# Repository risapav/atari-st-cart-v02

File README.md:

# Atari ST ROM Cartridge v2 — 2× W29C040-90B (16-bit)

**KiCad 10 project · Rev 1.2 · 2026-11-26 · risapav**  
https://github.com/risapav/atari-st-cart-v02

A read-only ROM cartridge PCB for the Atari ST/STE/Mega family.  
Two Winbond W29C040-90B Flash EEPROMs work in parallel to provide a full 16-bit data bus.  
A 4-position DIP switch (positions 1–3 active, position 4 unconnected) selects one of 8 banks of 128 KB, giving up to **1 MB** of banked ROM storage.

---

## Features

| Feature | Detail |
|---|---|
| Data bus | 16-bit (U1 → D0–D7 low byte, U2 → D8–D15 high byte) |
| ROM chips | 2× Winbond W29C040-90B (512 K × 8, DIP-32, 90 ns) |
| Total capacity | 1 MB (8 banks × 128 KB) |
| Address window | `$FA0000`–`$FBFFFF` (256 KB visible at once) |
| Bank switching | 4-bit DIP switch (SW1), positions 1–3 on chip A16–A18 (position 4 NC) |
| Chip select | Wired-AND of /ROM3 + /ROM4 via BAT42 diodes + 4.7 kΩ pull-up |
| Write-protect | /WE pulled to +5 V via R5 (10 kΩ) — the ST cannot write to the chip |
| Board size | 47.5 × 90.2 mm overall (42 mm-wide edge connector tongue) |
| Connector | 40-pin dual-row edge connector, 2 mm pitch (Atari CB101494) |

---

## Address Mapping

The Atari ST 68000 CPU does not expose A0 — byte selection is done through /UDS and /LDS.  
The cartridge port provides A1–A15, /ROM3, /ROM4, /UDS, /LDS, D0–D15.

```
ST bus signal   →   W29C040 pin
─────────────────────────────────
A1  – A15       →   A0  – A14   (15 bits)
/ROM4           →   A15         (0 = $FA bank, 1 = $FB bank)
SW1-1 (A16)     →   A16         ┐
SW1-2 (A17)     →   A17         ├ bank select (8 banks)
SW1-3 (A18)     →   A18         ┘
/ROM3 AND /ROM4 →   /CE (both chips, wired-AND)
/UDS            →   /OE on U2 (D8–D15, high byte chip)
/LDS            →   /OE on U1 (D0–D7, low byte chip)
/WE             →   ROM_~{WE} → R5 (10 kΩ) → +5V    write-protect
```

The full 256 KB window (`$FA0000`–`$FBFFFF`) is split by the /ROM4 signal:

| /ROM4 | /ROM3 | Region | Chip A15 |
|---|---|---|---|
| LOW  | HIGH | `$FA0000`–`$FAFFFF` | 0 |
| HIGH | LOW  | `$FB0000`–`$FBFFFF` | 1 |

Both chips are enabled only when **both** /ROM3 and /ROM4 are asserted (wired-AND through D1, D2).

---

## Bank Selection (DIP Switch SW1)

Switch closed = 0 (GND via switch) · Switch open = 1 (pulled to +5 V via 10 kΩ)

| SW1-3 | SW1-2 | SW1-1 | Bank | Offset in chip |
|---|---|---|---|---|
| 0 | 0 | 0 | 0 | 0x000000 |
| 0 | 0 | 1 | 1 | 0x010000 |
| 0 | 1 | 0 | 2 | 0x020000 |
| 0 | 1 | 1 | 3 | 0x030000 |
| 1 | 0 | 0 | 4 | 0x040000 |
| 1 | 0 | 1 | 5 | 0x050000 |
| 1 | 1 | 0 | 6 | 0x060000 |
| 1 | 1 | 1 | 7 | 0x070000 |

Each bank holds 128 KB visible through the ST cartridge window.  
U1 and U2 must be programmed independently (each chip carries one byte of every 16-bit word).  
Each chip holds 64 KB per bank (0x10000 bytes); the combined 16-bit content per bank is 128 KB.

---

## Bill of Materials

| Ref | Value / Part | Package | LCSC | Note |
|---|---|---|---|---|
| U1, U2 | Winbond W29C040-90B | DIP-32 W15.24 mm | C2331 | 512 K × 8 Flash EEPROM; U1 = low byte (D0–D7, /LDS), U2 = high byte (D8–D15, /UDS) |
| J1 | Atari ST cartridge port | 2×20 edge, 2 mm pitch | — | CB101494 compatible |
| SW1 | 4-pos slide DIP switch (pin 4 NC) | THT W7.62 mm P2.54 mm | — | bank select A16–A18 on positions 1–3 |
| D1, D2 | BAT42 | SOD-123 SMD | C134396 | wired-AND for /CE |
| R1 | 10 kΩ | 0805 SMD | C100047 | pull-up for chip A16 |
| R2 | 10 kΩ | 0805 SMD | C100047 | pull-up for chip A17 |
| R3 | 10 kΩ | 0805 SMD | C100047 | pull-up for chip A18 (also VPP for TC57H1000) |
| R4 | 4.7 kΩ | 0805 SMD | C60816 | pull-up on /CE wired-AND node |
| R5 | 10 kΩ | 0805 SMD | C100047 | pull-up for /WE (ROM_~{WE}) |
| C1, C2 | 100 nF | 0805 SMD | C83055 | decoupling, one per chip |
| C3 | 22 µF | THT radial D5 mm P2 mm | C43845 | bulk decoupling |
| JP1 | SolderJumper_2_Open | SMD 2-pad | — | bank-select tie-off; keep OPEN when using TC57H1000AD |

### Alternative chip: TC57H1000AD-85

The TC57H1000AD-85 (Toshiba 1 M × 8 SRAM) can be substituted with these adjustments:

| SW1 position | Setting | Reason |
|---|---|---|
| SW1-3 (A18 / VPP) | **open** | VPP must be +5 V; R3 pull-up provides this |
| SW1-2 (A17 / pin 30) | ignore | pin 30 is NC on TC57H1000 |
| SW1-1 (A16) | as desired | active bank select |

---

## Chip Enable Logic

```
/ROM3 ──|<|── D2 ──┬── R4 ── +5V
                   │
/ROM4 ──|<|── D1 ──┴── /CE (U1 pin 22, U2 pin 22)
```

`|<|` = Cathode (K) on the signal side, Anode (A) on the /CE node side.

Diodes D1 and D2 perform a passive wired-OR on active-low signals: /CE goes LOW whenever **either** /ROM3 or /ROM4 is LOW.  
When both signals are HIGH (no access), R4 (4.7 kΩ) holds /CE HIGH (chips deselected).  
In practice /ROM3 and /ROM4 are never both LOW simultaneously on the ST bus, so this effectively enables the chips when EITHER region is accessed.

---

## Repository Contents

```
cart_v02/
├── cart_v02.kicad_pro      — KiCad 10 project file
├── cart_v02.kicad_sch      — schematic
├── cart_v02.kicad_pcb      — PCB layout
├── my-libs/                — project-local symbol and footprint libraries
├── production/             — fabrication output (rev 1.1)
│   ├── Atari_ST_ROM_Cartridge_v2__2_W29C040-90B_16-bit_1.2.zip
│   ├── bom.csv
│   ├── designators.csv
│   ├── netlist.ipc
│   ├── positions.csv
│   └── JLCPCB_ORDER.md     — JLCPCB order parameters and procedure
├── tools/                  — Python scripts for ROM image preparation
│   ├── chips.py            — chip definitions (W29C040, TC57H1000)
│   ├── rom_pack.py         — pack directory or file list → chip files (STC auto-strip)
│   ├── rom_split.py        — split combined 16-bit image → LO + HI
│   ├── rom_info.py         — display bank map and chip statistics
│   ├── rom_validate.py     — validate ROM files (.bin/.stc/.rom/.img): size, magic, STC strip
│   ├── Makefile            — shortcuts: pack / split / info / validate (PRGDIR=prg/)
│   ├── README.md           — full tool documentation (SK)
│   ├── README_en.md        — full tool documentation (EN)
│   └── prg/                — source ROM images (default input for make pack)
├── doc/
│   ├── functional_analysis.md    — address decoding, CE logic, ROM formats (EN)
│   └── functional_analysis_sk.md — address decoding, CE logic, ROM formats (SK)
└── test/                   — virtual cartridge simulation (Python)
    ├── cartridge_model.py  — hardware model of the cartridge bus
    ├── generate_test_roms.py
    ├── run_tests.py        — 73 tests: address decode, bank switch, CE logic
    └── TESTING.md          — test methodology and results
```

### KiCad library dependency

Custom symbols and footprints are bundled inside `my-libs/` and referenced with `${KIPRJMOD}` paths in `fp-lib-table` and `sym-lib-table`.  
No global library installation is needed — just open `cart_v02.kicad_pro` directly.

---

## Programming the Chips

Each chip is 512 K × 8 and must be programmed **out of circuit** (remove from DIP socket).

The `tools/` directory contains Python scripts that automate all preparation steps:

Place all source ROM images (`.bin`, `.rom`, `.img`, `.stc`) into `tools/prg/`.
The tools use this directory as the default source location.

```bash
cd tools/

# Validate source images
python3 rom_validate.py prg/

# Pack all images from prg/ → chip files  (directory scanned automatically,
# filenames with spaces handled correctly, Steem .STC headers stripped)
make pack
# — or equivalently: python3 rom_pack.py prg/
# → writes prg/pack_order.txt and out/bank{N}_{original_name} copies

# Display bank map and chip signatures
python3 rom_info.py out/chip_u1_lo.bin out/chip_u2_hi.bin
```

**To reorder banks:** edit `prg/pack_order.txt` (one filename per line) and run `make pack` again.  
The numbered copies in `out/bank{N}_*` always reflect the current bank assignment.

Or with an explicit file list / different directory:

```bash
make pack PRGDIR=myroms/
make pack SRCS="game.bin other.rom"   # no spaces in filenames
```

Manual procedure (without scripts):

1. Prepare two binary files by de-interleaving the combined ROM image:
   - `chip_u1_lo.bin` — odd bytes (D0–D7, lower byte) → **U1**
   - `chip_u2_hi.bin` — even bytes (D8–D15, upper byte) → **U2**
2. For a banked image, place each bank at offset `bank × 0x10000` in each chip file.
3. Program each chip file into the respective chip using any W29C040-compatible EEPROM programmer.
4. Insert chips with correct orientation (pin 1 at the notch end).
5. Set SW1 to the desired bank.

> The W29C040-90B supports in-system Software Data Protection (SDP).  
> Disable SDP before programming if your programmer requires it.

See `tools/README_en.md` (EN) or `tools/README.md` (SK) for full documentation including TC57H1000AD-85 support.

---

## License

Hardware design released under [CERN-OHL-P v2](https://ohwr.org/cern_ohl_p_v2.txt) (permissive).

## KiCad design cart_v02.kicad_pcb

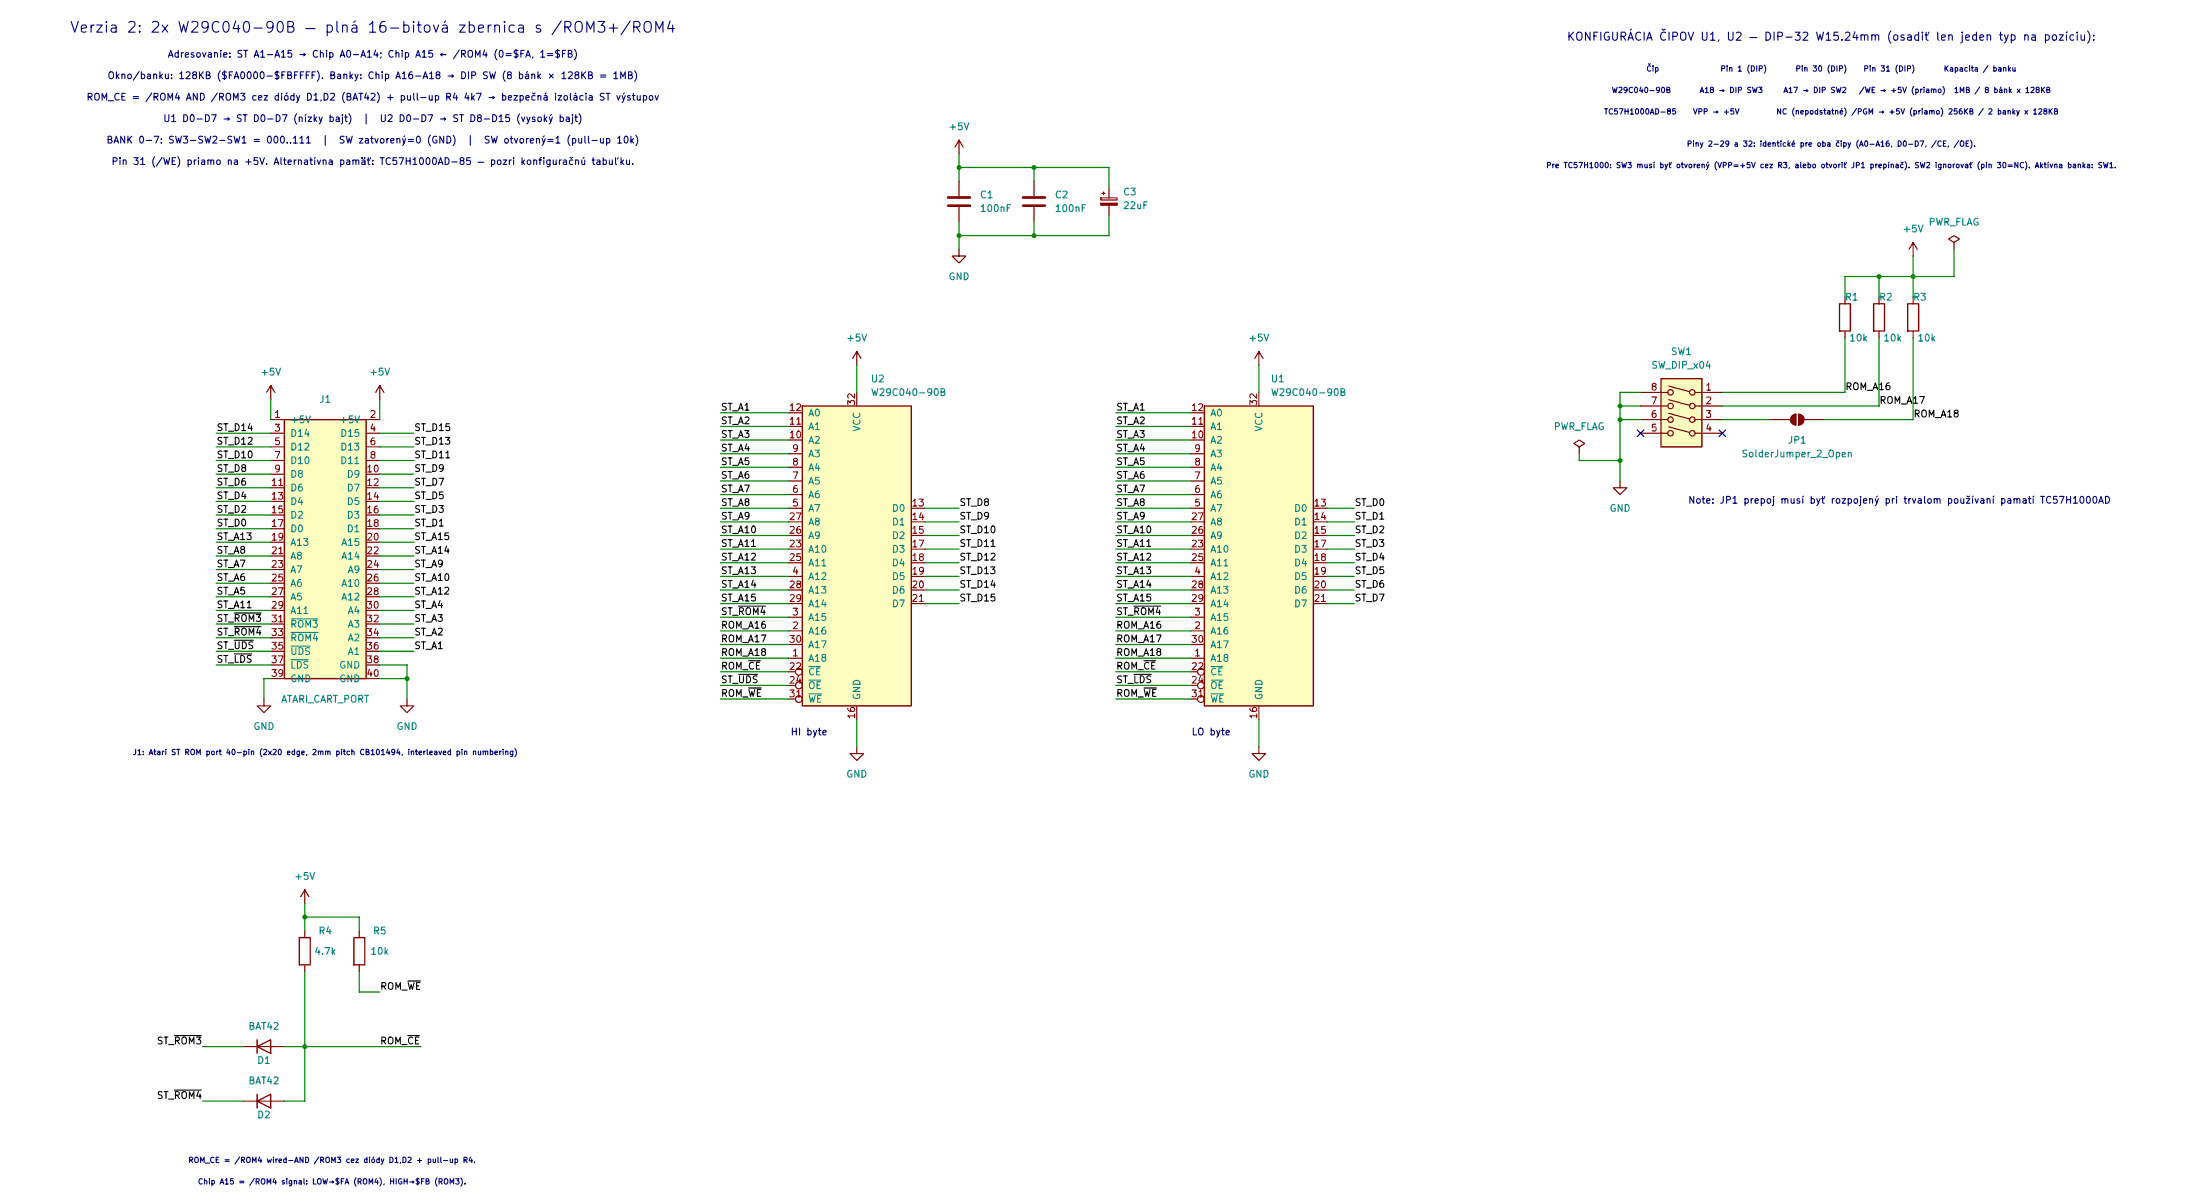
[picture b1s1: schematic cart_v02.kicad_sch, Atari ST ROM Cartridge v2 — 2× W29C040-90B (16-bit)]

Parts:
C1, C2: 100nF; C_0805_2012Metric; LCSC C83055
C3: 22uF; CP_Radial_D5.0mm_P2.00mm; LCSC C43845
D1, D2: BAT42; D_SOD-123; LCSC C134396
J1: ATARI_CART_PORT; ATARI_ST_CART
JP1: SolderJumper_2_Open; SolderJumper-2_P1.3mm_Open_RoundedPad1.0x1.5mm
R1, R2, R3, R5: 10k; R_0805_2012Metric_Pad1.20x1.40mm_HandSolder; LCSC C100047
R4: 4.7k; R_0805_2012Metric_Pad1.20x1.40mm_HandSolder; LCSC C60816
SW1: SW_DIP_x04; SW_DIP_SPSTx04_Slide_9.78x12.34mm_W7.62mm_P2.54mm
U1, U2: W29C040-90B; DIP-32_W15.24mm; LCSC C2331

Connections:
+5V: C1.1, C2.1, C3.1, J1.1 (+5V), J1.2 (+5V), R1.1, R2.1, R3.1, R4.1, R5.1, U1.32 (VCC), U2.32 (VCC)
/ROM_A16: R1.2, SW1.1, U1.2 (A16), U2.2 (A16)
/ROM_A17: R2.2, SW1.2, U1.30 (A17), U2.30 (A17)
/ROM_A18: JP1.1 (A), R3.2, U1.1 (A18), U2.1 (A18)
/ROM_~CE: D1.2 (A), D2.2 (A), R4.2, U1.22 (~CE), U2.22 (~CE)
/ROM_~WE: R5.2, U1.31 (~WE), U2.31 (~WE)
/ST_A1: J1.36 (A1), U1.12 (A0), U2.12 (A0)
/ST_A2: J1.34 (A2), U1.11 (A1), U2.11 (A1)
/ST_A3: J1.32 (A3), U1.10 (A2), U2.10 (A2)
/ST_A4: J1.30 (A4), U1.9 (A3), U2.9 (A3)
/ST_A5: J1.27 (A5), U1.8 (A4), U2.8 (A4)
/ST_A6: J1.25 (A6), U1.7 (A5), U2.7 (A5)
/ST_A7: J1.23 (A7), U1.6 (A6), U2.6 (A6)
/ST_A8: J1.21 (A8), U1.5 (A7), U2.5 (A7)
/ST_A9: J1.24 (A9), U1.27 (A8), U2.27 (A8)
/ST_A10: J1.26 (A10), U1.26 (A9), U2.26 (A9)
/ST_A11: J1.29 (A11), U1.23 (A10), U2.23 (A10)
/ST_A12: J1.28 (A12), U1.25 (A11), U2.25 (A11)
/ST_A13: J1.19 (A13), U1.4 (A12), U2.4 (A12)
/ST_A14: J1.22 (A14), U1.28 (A13), U2.28 (A13)
/ST_A15: J1.20 (A15), U1.29 (A14), U2.29 (A14)
/ST_D0: J1.17 (D0), U1.13 (D0)
/ST_D1: J1.18 (D1), U1.14 (D1)
/ST_D2: J1.15 (D2), U1.15 (D2)
/ST_D3: J1.16 (D3), U1.17 (D3)
/ST_D4: J1.13 (D4), U1.18 (D4)
/ST_D5: J1.14 (D5), U1.19 (D5)
/ST_D6: J1.11 (D6), U1.20 (D6)
/ST_D7: J1.12 (D7), U1.21 (D7)
/ST_D8: J1.9 (D8), U2.13 (D0)
/ST_D9: J1.10 (D9), U2.14 (D1)
/ST_D10: J1.7 (D10), U2.15 (D2)
/ST_D11: J1.8 (D11), U2.17 (D3)
/ST_D12: J1.5 (D12), U2.18 (D4)
/ST_D13: J1.6 (D13), U2.19 (D5)
/ST_D14: J1.3 (D14), U2.20 (D6)
/ST_D15: J1.4 (D15), U2.21 (D7)
/ST_~LDS: J1.37 (~LDS), U1.24 (~OE)
/ST_~ROM3: D1.1 (K), J1.31 (~ROM3)
/ST_~ROM4: D2.1 (K), J1.33 (~ROM4), U1.3 (A15), U2.3 (A15)
/ST_~UDS: J1.35 (~UDS), U2.24 (~OE)
GND: C1.2, C2.2, C3.2, J1.38 (GND), J1.39 (GND), J1.40 (GND), SW1.6, SW1.7, SW1.8, U1.16 (GND), U2.16 (GND)
unnamed: JP1.2 (B), SW1.3

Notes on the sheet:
LO byte
KONFIGURÁCIA ČIPOV U1, U2 — DIP-32 W15.24mm (osadiť len jeden typ na pozíciu):
Čip Pin 1 (DIP) Pin 30 (DIP) Pin 31 (DIP) Kapacita / banku
W29C040-90B A18 → DIP SW3 A17 → DIP SW2 /WE → +5V (priamo) 1MB / 8 bánk x 128KB
TC57H1000AD-85 VPP → +5V NC (nepodstatné) /PGM → +5V (priamo) 256KB / 2 banky x 128KB
Piny 2-29 a 32: identické pre oba čipy (A0-A16, D0-D7, /CE, /OE).
Pre TC57H1000: SW3 musí byť otvorený (VPP=+5V cez R3, alebo otvoriť JP1 prepínač). SW2 ignorovať (pin 30=NC). Aktívna banka: SW1.
ROM_CE = /ROM4 wired-AND /ROM3 cez diódy D1,D2 + pull-up R4.
Chip A15 = /ROM4 signal: LOW→$FA (ROM4), HIGH→$FB (ROM3).
J1: Atari ST ROM port 40-pin (2x20 edge, 2mm pitch CB101494, interleaved pin numbering)
Verzia 2: 2x W29C040-90B — plná 16-bitová zbernica s /ROM3+/ROM4
Adresovanie: ST A1-A15 → Chip A0-A14; Chip A15 ← /ROM4 (0=$FA, 1=$FB)
Okno/banku: 128KB ($FA0000-$FBFFFF). Banky: Chip A16-A18 → DIP SW (8 bánk × 128KB = 1MB)
ROM_CE = /ROM4 AND /ROM3 cez diódy D1,D2 (BAT42) + pull-up R4 4k7 → bezpečná izolácia ST výstupov
U1 D0-D7 → ST D0-D7 (nízky bajt) | U2 D0-D7 → ST D8-D15 (vysoký bajt)
BANK 0-7: SW3-SW2-SW1 = 000..111 | SW zatvorený=0 (GND) | SW otvorený=1 (pull-up 10k)
Pin 31 (/WE) priamo na +5V. Alternatívna pamäť: TC57H1000AD-85 — pozri konfiguračnú tabuľku.
Note: JP1 prepoj musí byť rozpojený pri trvalom používaní pamatí TC57H1000AD
HI byte

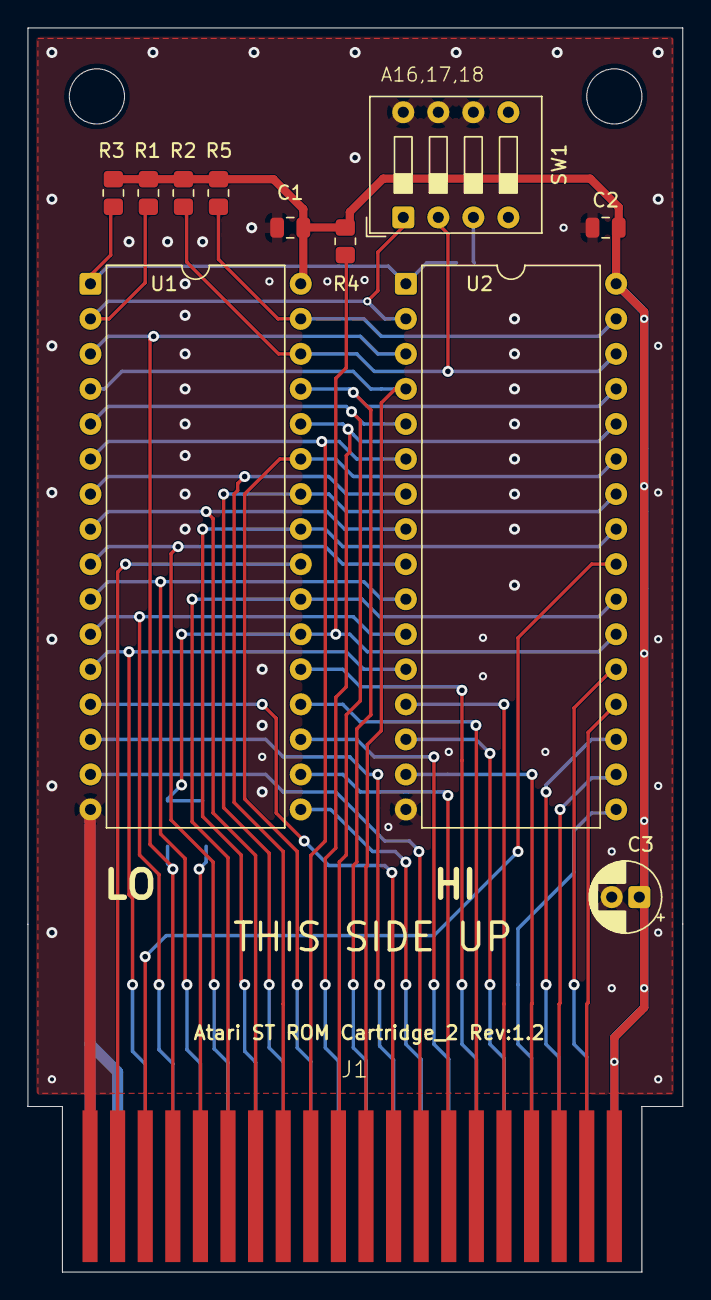
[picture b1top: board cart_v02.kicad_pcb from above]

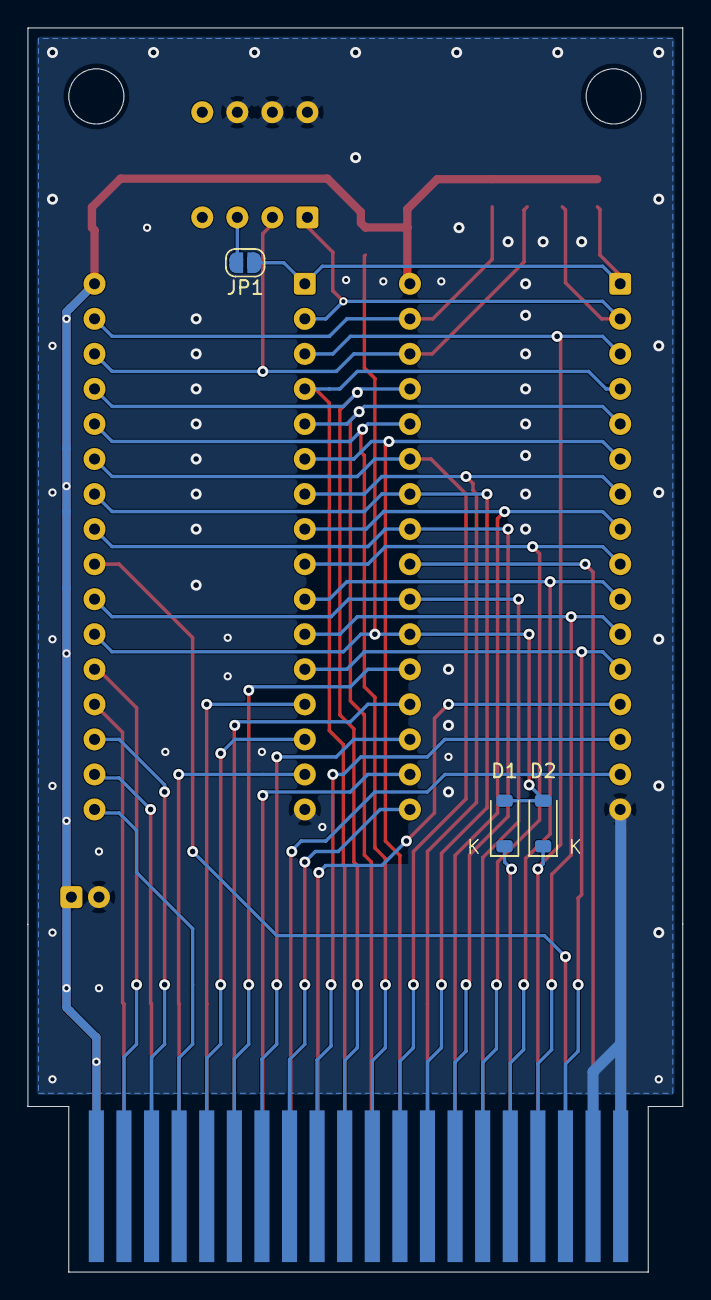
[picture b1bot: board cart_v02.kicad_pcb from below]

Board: 2 copper layers, 47.5 x 90.2 mm, 15 parts (3 on the bottom side), 43 nets.

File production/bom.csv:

Designator,Footprint,Quantity,Value,LCSC Part #
"C1, C2",0805,2,100nF,C83055
C3,CP_Radial_D5.0mm_P2.00mm,1,22uF,C43845
"D1, D2",D_SOD-123,2,BAT42,C134396
J1,ATARI_ST_CART,1,ATARI_CART_PORT,
"R1, R2, R3, R5",0805,4,10k,C100047
R4,0805,1,4.7k,C60816
SW1,SW_DIP_SPSTx04_Slide_9.78x12.34mm_W7.62mm_P2.54mm,1,SW_DIP_x04,
"U1, U2",DIP-32_W15.24mm,2,W29C040-90B,C2331
